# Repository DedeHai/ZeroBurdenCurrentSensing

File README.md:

# ZeroBurdenCurrentSensing
A circuit I made to measure the dynamically changing currents in low power microcontroller applications.

a detailed description is avialable on my blog: https://bashtelorofscience.wordpress.com/2017/11/05/zero-burden-voltage-current-amplifier/

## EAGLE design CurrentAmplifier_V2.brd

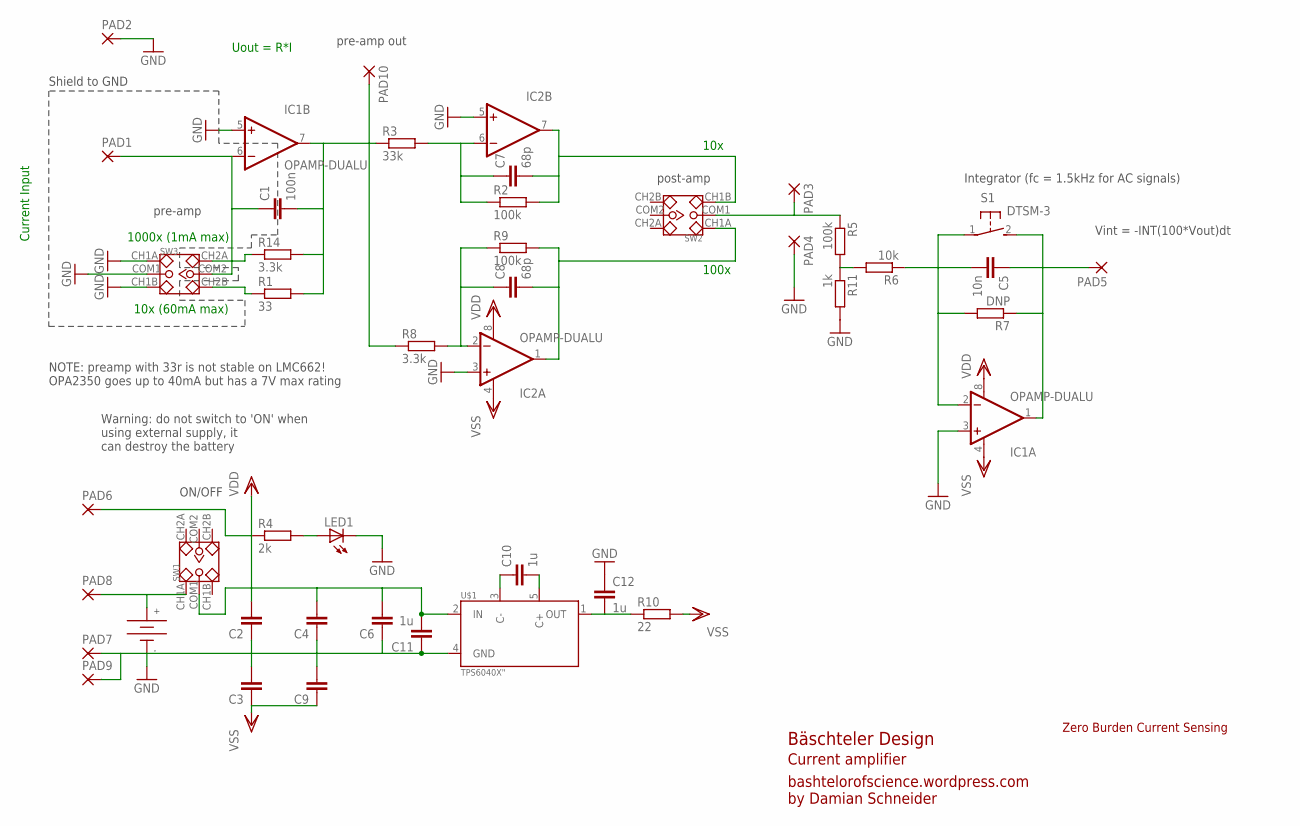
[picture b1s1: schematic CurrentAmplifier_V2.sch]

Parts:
C1: 100n; C0805K
C2, C3, C4: C-EUC0805; C0805
C5: 10n; C0805K
C6, C9: C-EUC1206; C1206
C7, C8: 68p; C0603
C10, C11, C12: 1u; C0603
CR1: DX_CR2032HANDSOLDER; DX_CR2032_SMD_HANDSOLDER
IC1, IC2: OPAMP-DUALU; SO08
LED1: LEDCHIP-LED0805; CHIP-LED0805
PAD1, PAD2, PAD3, PAD4, PAD5, PAD6, PAD7, PAD8, PAD9, PAD10: 1,6/0,9
R1: 33; R0805
R2, R5, R9: 100k; R0603
R3: 33k; R0603
R4: 2k; R0603
R6: 10k; R0603
R7: DNP; R0805
R8: 3.3k; R0603
R10: 22; R0805
R11: 1k; R0603
R14: 3.3k; R0805
S1: DTSM-3
SW1, SW2, SW3: DIP-TOGGLE-SWITCH-2CH-(2X3P-2.54); SW6-2.54-9.0X3.5X3.2+2.0MM
U$1: TPS6040X"; SOT23-5

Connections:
+: CR1.P$1 (+), PAD8.1, SW1.CH1A
GND: C2.1, C3.2, C4.1, C6.1, C9.2, C11.1, C12.1, CR1.P$2 (-), IC1.3 (+IN), IC1.5 (+IN), IC2.3 (+IN), IC2.5 (+IN), LED1.C, PAD2.1, PAD4.1, PAD7.1, PAD9.1, R11.2, SW3.CH1A, SW3.CH1B, SW3.COM1, U$1.4 (GND)
unnamed: C1.2, IC1.7 (OUT), PAD10.1, R1.2, R3.1, R8.1, R14.2
unnamed: C7.1, IC2.6 (-IN), R2.1, R3.2
unnamed: R5.2, R6.2, R11.1
unnamed: C7.2, IC2.7 (OUT), R2.2, SW2.CH1B
unnamed: R14.1, SW3.CH2A
unnamed: C10.1, U$1.3 (C-)
unnamed: C10.2, U$1.5 (C+)
unnamed: LED1.A, R4.2
unnamed: C5.2, IC1.2 (-IN), R6.1, R7.2, S1.1
unnamed: C5.1, IC1.1 (OUT), PAD5.1, R7.1, S1.2
unnamed: C8.1, IC2.2 (-IN), R8.2, R9.1
unnamed: C8.2, IC2.1 (OUT), R9.2, SW2.CH1A
unnamed: PAD3.1, R5.1, SW2.COM1
unnamed: C12.2, R10.1, U$1.1 (OUT)
unnamed: C1.1, IC1.6 (-IN), PAD1.1, SW3.COM2
unnamed: R1.1, SW3.CH2B
VDD: C2.2, C4.2, C6.2, C11.2, IC1.8 (V+), IC2.8 (V+), PAD6.1, R4.1, SW1.COM1, U$1.2 (IN)
VSS: C3.1, C9.1, IC1.4 (V-), IC2.4 (V-), R10.2

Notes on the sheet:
Uout = R*I
Current Input
Shield to GND
10x
100x
ON/OFF
post-amp
1000x (1mA max)
10x (60mA max)
pre-amp
Zero Burden Current Sensing
Integrator (fc = 1.5kHz for AC signals)
Warning: do not switch to 'ON' when using external supply, it can destroy the battery
Vint = -INT(100*Vout)dt
NOTE: preamp with 33r is not stable on LMC662! OPA2350 goes up to 40mA but has a 7V max rating
pre-amp out
Bäschteler Design
bashtelorofscience.wordpress.com by Damian Schneider
Current amplifier

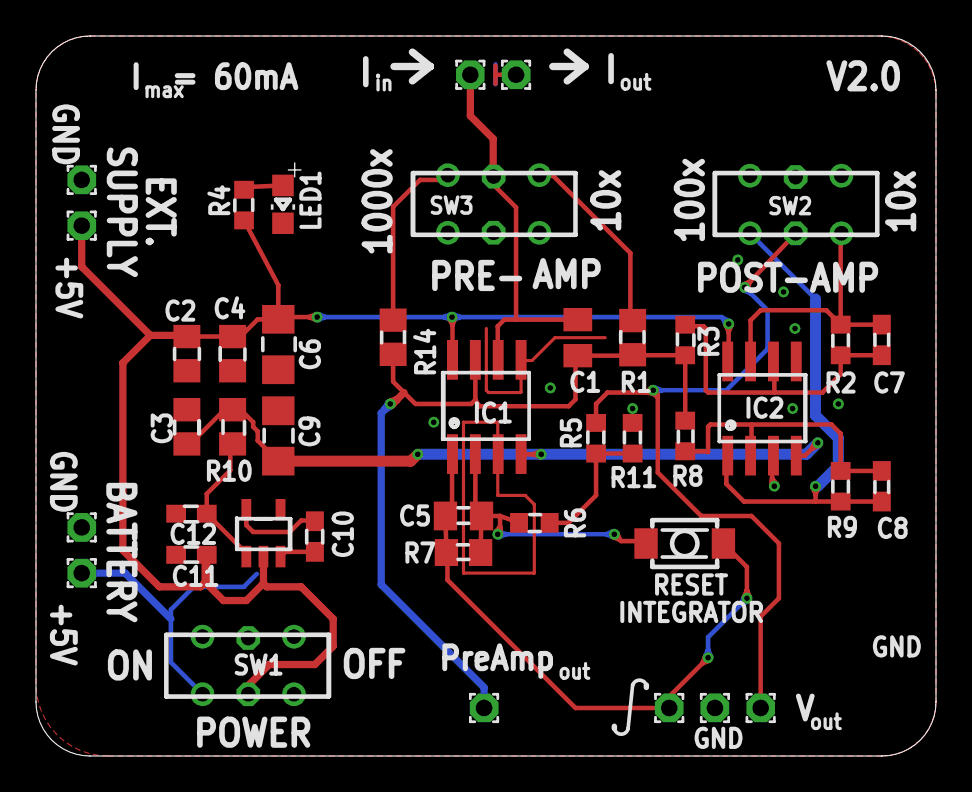
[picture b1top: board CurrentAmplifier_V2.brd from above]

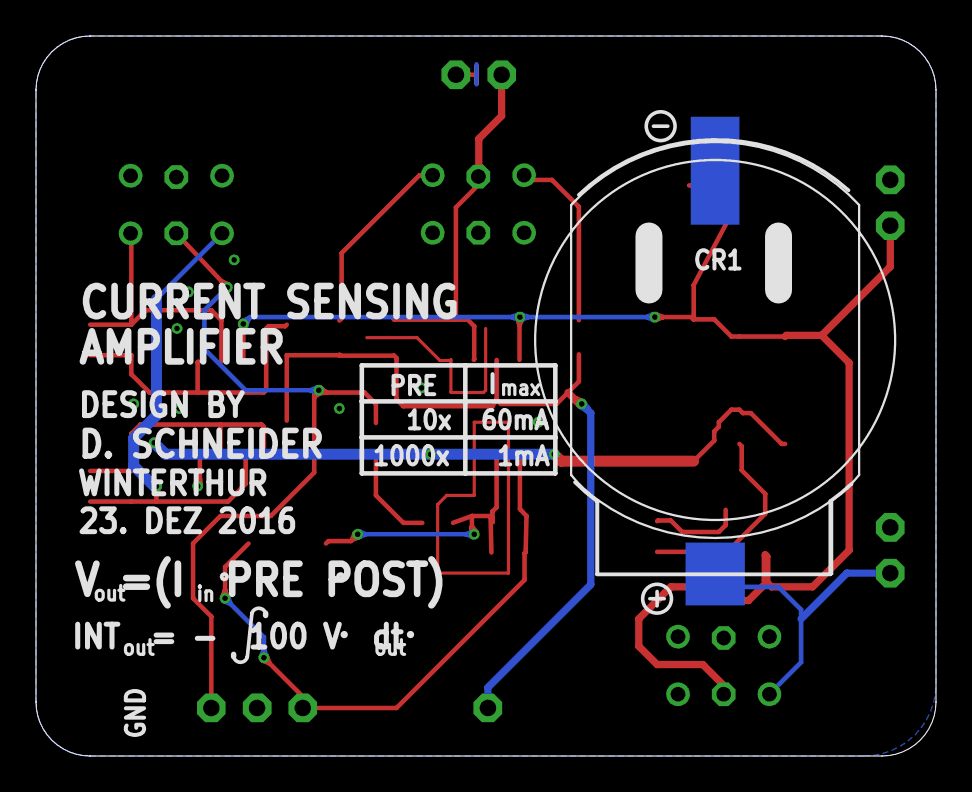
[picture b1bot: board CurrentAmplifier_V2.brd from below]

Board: 2 copper layers, 50.0 x 40.0 mm, 45 parts (3 on the bottom side), 20 nets.

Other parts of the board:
U$2: CC-BY-NC-SA_SR
U$5: OSH_LOGO_L_SR

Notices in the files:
parts and their libraries:
SparkFun-AnalogIC: Licensing:Creative Commons ShareAlike 4.0 International - https://creativecommons.org/licenses/by-sa/4.0
